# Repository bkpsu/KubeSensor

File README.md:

# KubeSensor
Kube - A modular, expandable home automation multi sensor platform

## Description

The Kube V2 builds on the previous [design](https://www.thingiverse.com/thing:2539897), incorporating improvements to modularity, support for additional sensors, and building ease.

##### Original Kube (left) and Kube V2 (right)

The main design improvement for Kube V2 is that all components are installed on dedicated PCBs, removing the need for wiring, and the PCBs are connected to each other via long headers, which allow the different "modules" to snap together to form a complete Kube.

##### OLED module (top) with male headers that snap into the base board (bottom) with tabs on the 3d printed enclosures holding the module in place

The 6-pin header is populated with I2C signals from the NodeMCU (D1/D2), D4 pin for LED control, and 5V and 3V3 power supply pins with ground. This allows building various different designs of the "stack", and future expansion of the Kube platform, via I2C connected "submodules". The design currently contains four modules, including:

1. Base module (with NodeMCU, breakout headers, 74HCT125N level shifter and external connectors/spots for DHT22 sensor)
2. Power Supply module (with AC/DC, DC/DC and POE-level power supply options, to provide the 5V power for the stack)
3. Analog/Digital IO module (offering expansion of Digital I/O up to 128 signals and 4 channels of 16-bit ADC analog)
4. OLED/AmbiMate sensor module (offering a 0.96" OLED screen for local sensor data display and support for the multiple sensor AmbiMate MS4 board from TE Connectivity)

##### Kube stack with boards 1 (Base Module) and 4 (OLED/AmbiMate) shown, comprising a multi sensor

The different boards can be stacked in any order (with OLED board on top, of course), and multiple ADIO boards can be stacked together to expand I/O up to 128 channels.

The Kube v2 supports typical ESP8266 firmwares, including [ESPEasy](https://www.letscontrolit.com/wiki/index.php?title=ESPEasy), as well as my original Kube [firmware](https://github.com/bkpsu/NodeMCU-Home-Automation-Sensor) (with minor changes for pin layout). With ESPEasy, the different sensors and OLED screen can be easily connected to home automation platofrms like [openHAB](https://www.openhab.org) or [HomeAssistant](https://www.home-assistant.io/) via MQTT.

---

## Boards

This section will describe the currently available Kube module boards in detail, including schematics and any jumper settings required for each board, as well as links to the parts required to build each module.

### 1. Kube Base Module

The Kube Base module is the only **required** board in the Kube stack. It contains the headers for a [NodeMCU](https://amzn.to/2l9GGET) v0.9, v2 (LoLin v3 works, but won't fit the enclosure), as well as breakout headers for all of the NodeMCU pins. With just the Kube Base module, a NodeMCU, a DHT22 sensor, and an OLED screen, you can create [this sensor](https://www.thingiverse.com/thing:2539897):

The base module contains the following features/headers:

**TOP**: (NodeMCU side)

|Device|Usage|Notes|
|:--------|:-----|-------|
|EXT|Used for external sensor connections, e.g. [HC-SR501](https://amzn.to/2l9G0zl) PIR motion sensor (D5 NodeMCU pin)|VCC pin is tied to JP1, sourcing either 3.3V or 5V DC|
|JP1|Selects 5V or 3.3V supply voltage for the EXT header|Does *not* affect D5 pin voltage range|
|IC1|[74HCT125N](https://amzn.to/2l9FBwP) 4-channel fast level shifter|Used for I2C/LED and EXT signal pins; Great for LED pixels|
|D1|[BAT43](https://amzn.to/2jFCRqv) Schottky Diode|Used between RST and D0 pins on the NodeMCU to prevent boot-up issues during flashing|
|DHT|[DHT22](https://amzn.to/2l98yZL) Temperature/Humidity sensor|Used when base baord is used as a remote temperature/humidity sensor; uses D6 pin on NodeMCU|
|I2C/LED|I2C bus connector header, to allow *daughter-boards* to connect to the Kube base board and to each other|Has both 5V and 3.3V pins, GND, SCL (D1) and SDA (D2), as well as an additional digital I/O pin (D4), commonly used in LED strip controller firmware|

**BOTTOM**:

|Device|Usage|Notes|
|:--------|:-----|-------|
|D1BYP, D2BYP|Used to shift (to 5V via IC1) or bypass (3.3V from the NodeMCU) the I2C Clock (D1, SCL) and Data (D2, SDA) pins within the I2C/LED header|Solder middle pad to either the SHFT (for 5V) or BYP (for 3.3v) pads.|
|D4BYP|Used to shift (to 5V via IC1) or bypass (3.3V from the NodeMCU) the D4 LED pin within the I2C/LED header|Solder middle pad to either the SHFT (for 5V) or BYP (for 3.3v) pads.|
|D5BYP|Used to shift (to 5V via IC1) or bypass (3.3V from the NodeMCU) the D5 EXT pin within the EXT sensor header|Solder middle pad to either the SHFT (for 5V) or BYP (for 3.3v) pads.|

The full schematic for the Kube baseboard is shown below: 

### 2. Power Supply Module

The Kube Power supply submodule offers several options to provide the 5VDC power required to run the NodeMCU and the entire Kube stack. It is *generally* not required, since it's perfectly fine to power the Kube with just a USB power supply via the NodeMCU's micro-USB port (accessible via a hole in the base module's enclosure), but if you're going to use more sensors, IO boards, or other external devices, it *is recommended* to supply power to the Kube stack via this PSU board module.

The Kube PS board module provides three possible configurations, each allowing different input voltages, with 5V DC output.

1. Using a [MeanWell IRM-03-5](https://amzn.to/2lbSsym) AC/DC power supply (110VAC in, 5VDC out) for a wall-pluggable unit
2. Using [MeanWell SLC03x](https://www.arrow.com/en/products/slc03b-05/mean-well-enterprises) series DC-DC power supplies for multiple input options (12j/24VDC, Power-over-Ethernet, etc)
3. Using a [Rectifier](https://amzn.to/2lin9SL) and a [Buck Converter](https://amzn.to/2lkQhZH) to convert low-voltage AC (e.g. a door bell transformer or HVAC thermostat power) to power the kube stack.

***NOTE***: **BE EXTREMELY CAREFUL WHEN USING THE KUBE PS MODULE WITH AC POWER. THE PCB TRACES ON THE BOTTOM OF THE BOARD WILL HAVE LIVE AC VOLTAGE ON THEM. IT IS BEST TO KEEP THE UNIT UNPLUGGED WHILE ASSEMBLING/DISSASEMBLING THE KUBE STACK.**

Regardless of which of the 3 power methods you're using, the power input wiring will go through the [2-pin screw terminal](https://amzn.to/2lhCMtC) (X1), with Line or DC+ on the left terminal, and Neutral or DC- on the right terminal. The line/DC+ line is [fuse-protected](https://amzn.to/2jPolfY) prior to going to the power supplies. Secure the input wiring with a zip-tie through the two holes drilled below the X1 connector.

The full schematic for the Kube Power Supply submodule is shown below:

### 3. Analog/Digital I/O module

The ADIO Kube submodule can be used when more I/O is required than the NodeMCU GPIO pins provide, or for a more precise way to bring in analog inputs into the Kube sensor.

The ADIO submodule provides space for the [MCP23017](https://amzn.to/2lg6Qpt) 16-channel digital I/O expander, as well as a [ADS1115](https://amzn.to/2lgUYDz) 4-channel 16-bit analog ADC module. In addition, the MCP23017 address pins have been broken out into three headers (AD0, AD1, AD2), which allow addressing up to 8 different MCP23017 chips. In theory, you could stack 8 ADIO submoodules in the Kube stack, for a total of 128 digital I/O pins!

##### Testing a full Kube stack with an analog differential pressure sensor connected to the ADIO submodule.

The MCP23017 addressing is handled via jumpers on the AD0, AD1 and AD2 headers. Jumpering the left pin to the middle pin sets that address bit HIGH (1) and jumpering the right pin to the middle pin sets it LOW (0). The following table shows the complete I2C address scheme based on jumper settings:

|AD0|AD1|AD2|I2C Address|
|---|---|---|-----|
|0|0|0|0x20|
|1|0|0|0x21|
|0|1|0|0x22|
|1|1|0|0x23|
|0|0|1|0x24|
|1|0|1|0x25|
|0|1|1|0x26|
|1|1|1|0x27|

The ADS1115 board is also addressable, using the AADDR headers. Select addresses 0x48, 0x49, 0x4A or 0x4B by placing a jumper across one set of the jumper pins. This way, up to 4 ADIO submodules may have ADS1115 breakouts installed, for a total of 16 analog input channels.

The rest of the devices on the ADIO submodule are described below:

|Device|Usage|Notes|
|:--------|:-----|-------|
|IC1|[MCP23017](https://amzn.to/2lg6Qpt) I/O Expander|16 channel digital I/O expander|
|ADS1115|[ADS1115](https://amzn.to/2lgUYDz)|4 channel 16-bit analog ADC module (can also use [ADS1015](https://amzn.to/2lcyVOj), 12-bit ADC)|
|X1|Channels 1 through 4 (top to bottom) of the MCP23017|Wired in using [4-pin screw terminals](https://amzn.to/2lc5hbY)|
|X2|Channels 5 through 8 (top to bottom) of the MCP23017|Wired in using [4-pin screw terminals](https://amzn.to/2lc5hbY)|
|X3|Channels 9 through 12 (top to bottom) of the MCP23017|Wired in using [4-pin screw terminals](https://amzn.to/2lc5hbY)|
|X4|Channels 13 through 16 (top to bottom) of the MCP23017|Wired in using [4-pin screw terminals](https://amzn.to/2lc5hbY)|
|X5|Channels 1 through 4 (top to bottom) of the ADS1115|Wired in using [4-pin screw terminals](https://amzn.to/2lc5hbY)|
|X6 & X7|GND terminals for the I/O signals|Wired in using [4-pin screw terminals](https://amzn.to/2lc5hbY)|
|X8|5V power terminals for the I/O signals|Wired in using [4-pin screw terminals](https://amzn.to/2lc5hbY)|
|I2C/LED|I2C bus connector header, to allow *daughter-boards* to connect to the Kube base board and to each other|Has both 5V and 3.3V pins, GND, SCL (D1) and SDA (D2), as well as an additional digital I/O pin (D4), commonly used in LED strip controller firmware|

The full schematic for the Kube IO submodule is shown below:

### 4. OLED/AmbiMate MS4 module

The OLED/AmbiMate submodule serves a dual purpose. It can provide a local display of all the Kube sensor values (if the OLED screen is installed), and with the optional TE AmbiMate MS4 sensor board installed, it can read values such as temperature/humidity/light/audio level/motion/CO2 level/VOCs level, and provide them via I2C to the NodeMCU. In lieu of the TE Ambimate MS4, a space is provided for the cheaper (but still very precise) BME280/BMP280 sensor board.

The [OLED display](https://amzn.to/2ll4BkL) used (0.96") provides a good canvas for displaying local sensor data. However, the boards used with these displays are not always standard. I have seen multiple versions of these boards, with different pinouts for the 4 pin i2C interface, e.g. GND/VCC/SCL/SDA or VCC/GND/SCL/SDA. To allow both boards to be installed on the submodule, there are 4 jumpers on the back of the board, that allow swapping of the GND/VCC pins, and SCL/SDA pins, to hopefully match any combination of pins on the widely available modules.

The devices that fit on this board are as follows:

**TOP**:

|Device|Usage|Notes|
|:--------|:-----|-------|
|OLED|[OLED 0.96" Display](https://amzn.to/2ll4BkL)|16 channel digital I/O expander|
|TE AmbiMate MS4 Sensor|[Full Version](https://www.arrow.com/en/products/2316852-2/te-connectivity) or [Base Version](https://www.arrow.com/en/products/2316851-1/te-connectivity) (Temp/Humidity/Light/Motion only)|Multi-sensor from TE, with temperature/humidity/motion/light/CO2/VOCs and audio level measurements|
|I2C/LED|I2C bus connector header, to allow *daughter-boards* to connect to the Kube base board and to each other|Has both 5V and 3.3V pins, GND, SCL (D1) and SDA (D2), as well as an additional digital I/O pin (D4), commonly used in LED strip controller firmware|
|BMX280|[BME280/BMP280](https://amzn.to/2ZcHmcq) I2C sensor connector header|Jumper SJ5 to correct VCC (3v3 or 5V) for your sensor|

**BOTTOM**:

|Device|Usage|Notes|
|:--------|:------|-------|
|SJ1|First OLED pin selector|Match GND or VCC with your OLED screen's first pin, and solder that side to the middle pad|
|SJ2|Second OLED pin selector|Match GND or VCC with your OLED screen's second pin, and solder that side to the middle pad|
|SJ3|Third OLED pin selector|Match SCL or SDA with your OLED screen's third pin, and solder that side to the middle pad|
|SJ4|Fourth OLED pin selector|Match SCL or SDA with your OLED screen's fourth pin, and solder that side to the middle pad|
|SJ5|BMx280 sensor VCC selector|If using the 4-pin (5V) unit, jumper middle pad to 5v pad, and for 6-pin (3v3) unit, jumper middle pad to 3v3 pad|

The full schematic for the Kube OLED/AmbiMate submodule is shown below:

---

## Software

Use [ESPEasy](https://www.letscontrolit.com/espeasy/) firmware to easily connect the different sensors to the NodeMCU, and send them to your favorite database, or home automation program.

---

## BOM

Full, up to date BOM is available [here](Kube_V2_BOM.xlsx).

Get the PCB Boards directly from [PCBWay](https://www.pcbway.com/project/member/?bmbno=74C10494-455E-47)!

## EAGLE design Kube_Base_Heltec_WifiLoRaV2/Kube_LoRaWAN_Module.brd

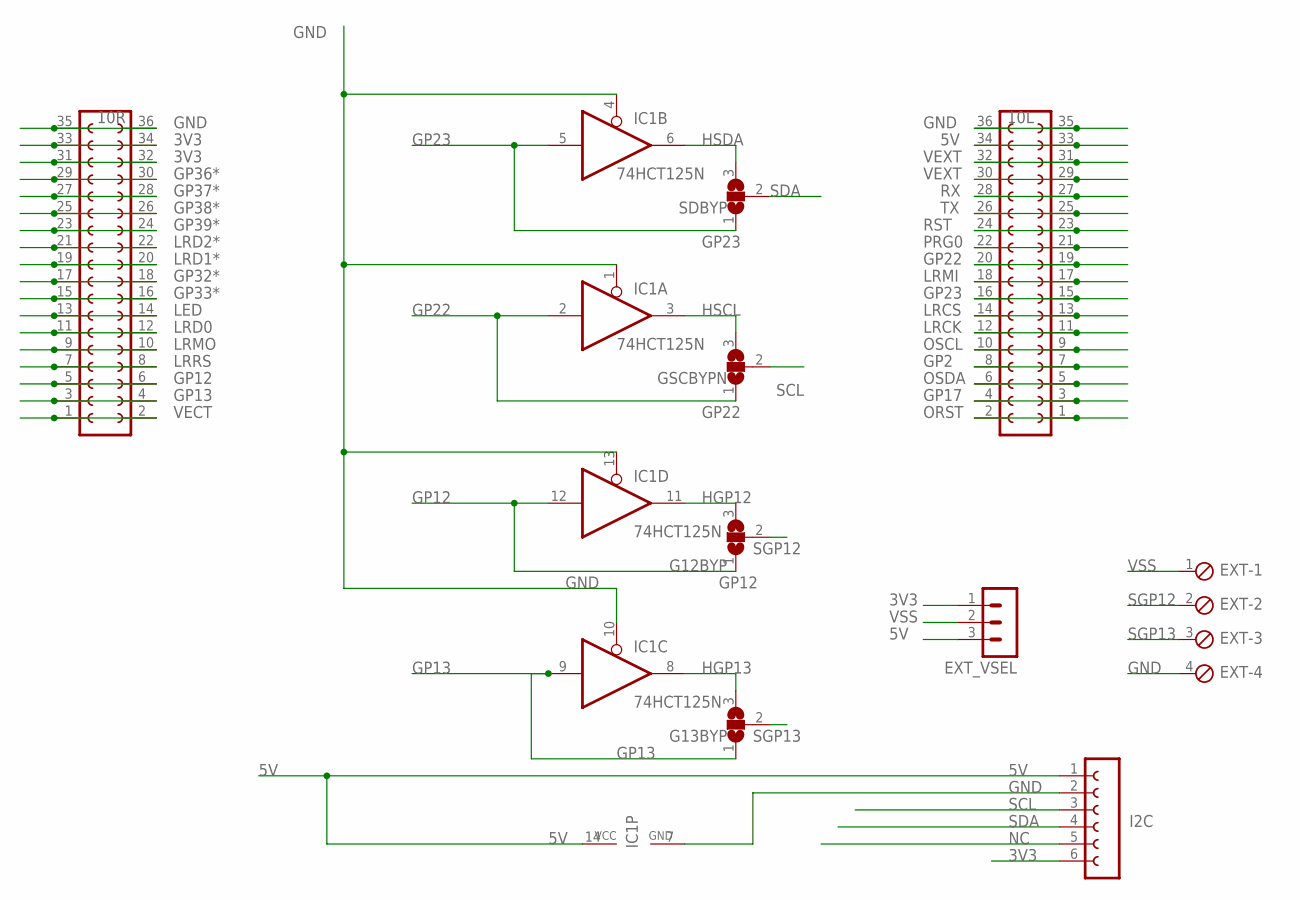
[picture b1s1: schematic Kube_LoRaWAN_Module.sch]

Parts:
10L, 10R: 15; FE18-2
EXT: MPT4; 4POL254
EXT_VSEL: MA03-1
G12BYP, G13BYP: SJ2W; SJ_2
GSCBYPN: SJ2W; SJ_2
I2C: FE06-1; FE06
IC1: 74HCT125N; DIL14
SDBYP: SJ2W; SJ_2

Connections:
3V3: 10R.31, 10R.32, 10R.33, 10R.34, EXT_VSEL.1, I2C.6
5V: 10L.33, 10L.34, EXT_VSEL.3, I2C.1, IC1.14 (VCC)
GND: 10L.35, 10L.36, 10R.35, 10R.36, EXT.4, I2C.2, IC1.1 (OE), IC1.4 (OE), IC1.7 (GND), IC1.10 (OE), IC1.13 (OE)
GP2: 10L.7, 10L.8
GP12: 10R.5, 10R.6, G12BYP.1, IC1.12 (I)
GP13: 10R.3, 10R.4, G13BYP.1, IC1.9 (I)
GP17: 10L.3, 10L.4
GP22: 10L.19, 10L.20, GSCBYPN.1, IC1.2 (I)
GP23: 10L.15, 10L.16, IC1.5 (I), SDBYP.1
GP32*: 10R.17, 10R.18
GP33*: 10R.15, 10R.16
GP36*: 10R.29, 10R.30
GP37*: 10R.27, 10R.28
GP38*: 10R.25, 10R.26
GP39*: 10R.23, 10R.24
HGP12: G12BYP.3, IC1.11 (O)
HGP13: G13BYP.3, IC1.8 (O)
HSCL: GSCBYPN.3, IC1.3 (O)
HSDA: IC1.6 (O), SDBYP.3
LED: 10R.13, 10R.14
LRCK: 10L.11, 10L.12
LRCS: 10L.13, 10L.14
LRD0: 10R.11, 10R.12
LRD1*: 10R.19, 10R.20
LRD2*: 10R.21, 10R.22
LRMI: 10L.17, 10L.18
LRMO: 10R.9, 10R.10
LRRS: 10R.7, 10R.8
NC: I2C.5
ORST: 10L.1, 10L.2
OSCL: 10L.9, 10L.10
OSDA: 10L.5, 10L.6
PRG0: 10L.21, 10L.22
RST: 10L.23, 10L.24
RX: 10L.27, 10L.28
SCL: GSCBYPN.2, I2C.3
SDA: I2C.4, SDBYP.2
SGP12: EXT.2, G12BYP.2
SGP13: EXT.3, G13BYP.2
TX: 10L.25, 10L.26
VECT: 10R.1, 10R.2
VEXT: 10L.29, 10L.30, 10L.31, 10L.32
VSS: EXT.1, EXT_VSEL.2

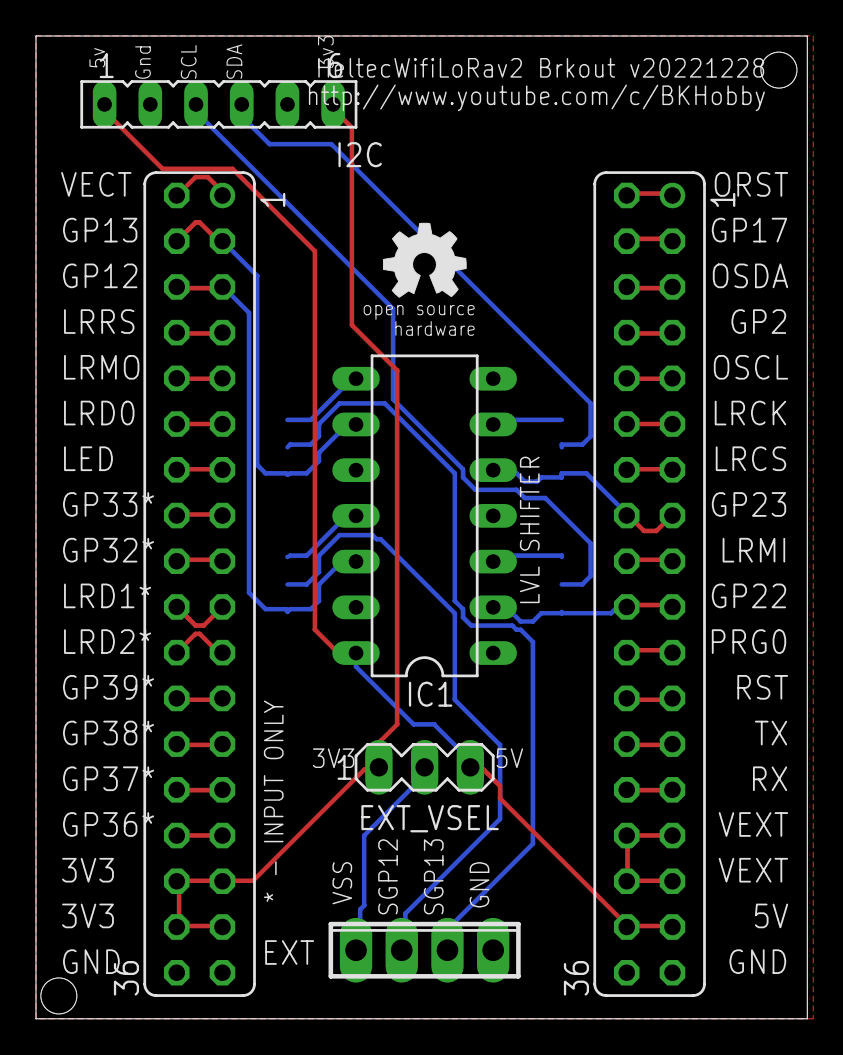
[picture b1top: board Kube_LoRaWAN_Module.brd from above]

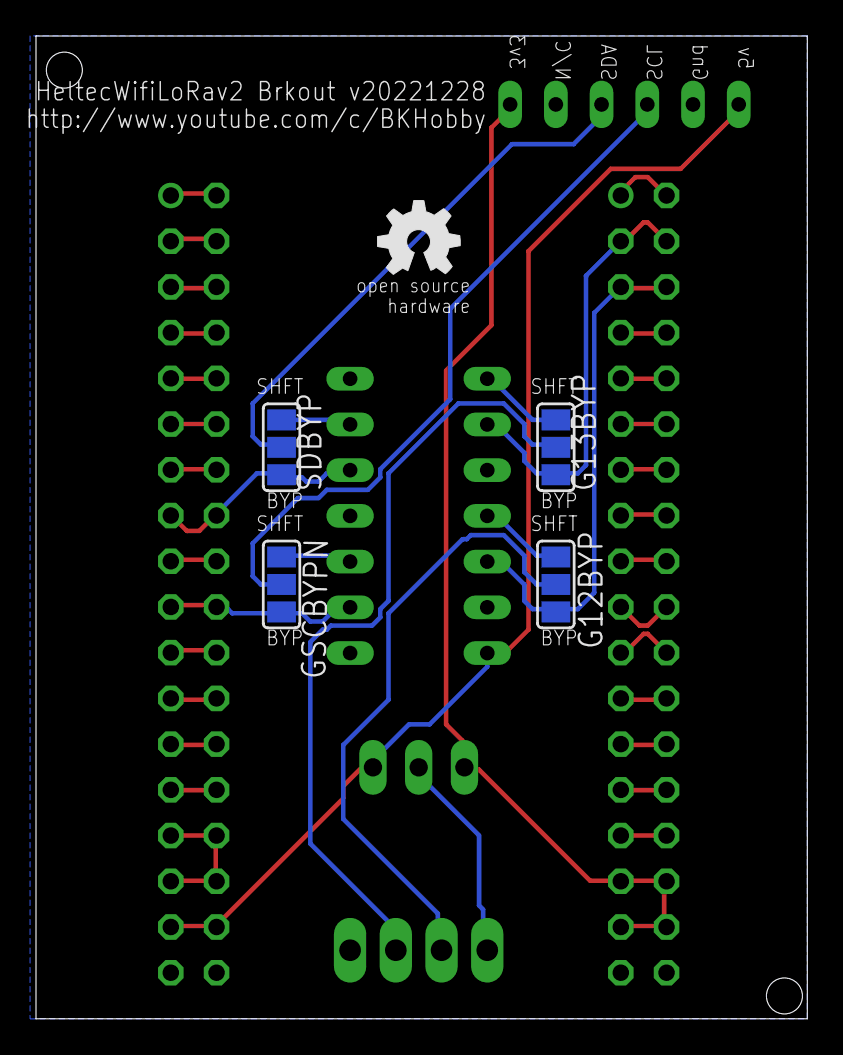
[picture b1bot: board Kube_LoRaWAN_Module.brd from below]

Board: 2 copper layers, 42.8 x 54.6 mm, 12 parts (5 on the bottom side), 42 nets.

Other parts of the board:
U$1, U$2: OSHW_5MM

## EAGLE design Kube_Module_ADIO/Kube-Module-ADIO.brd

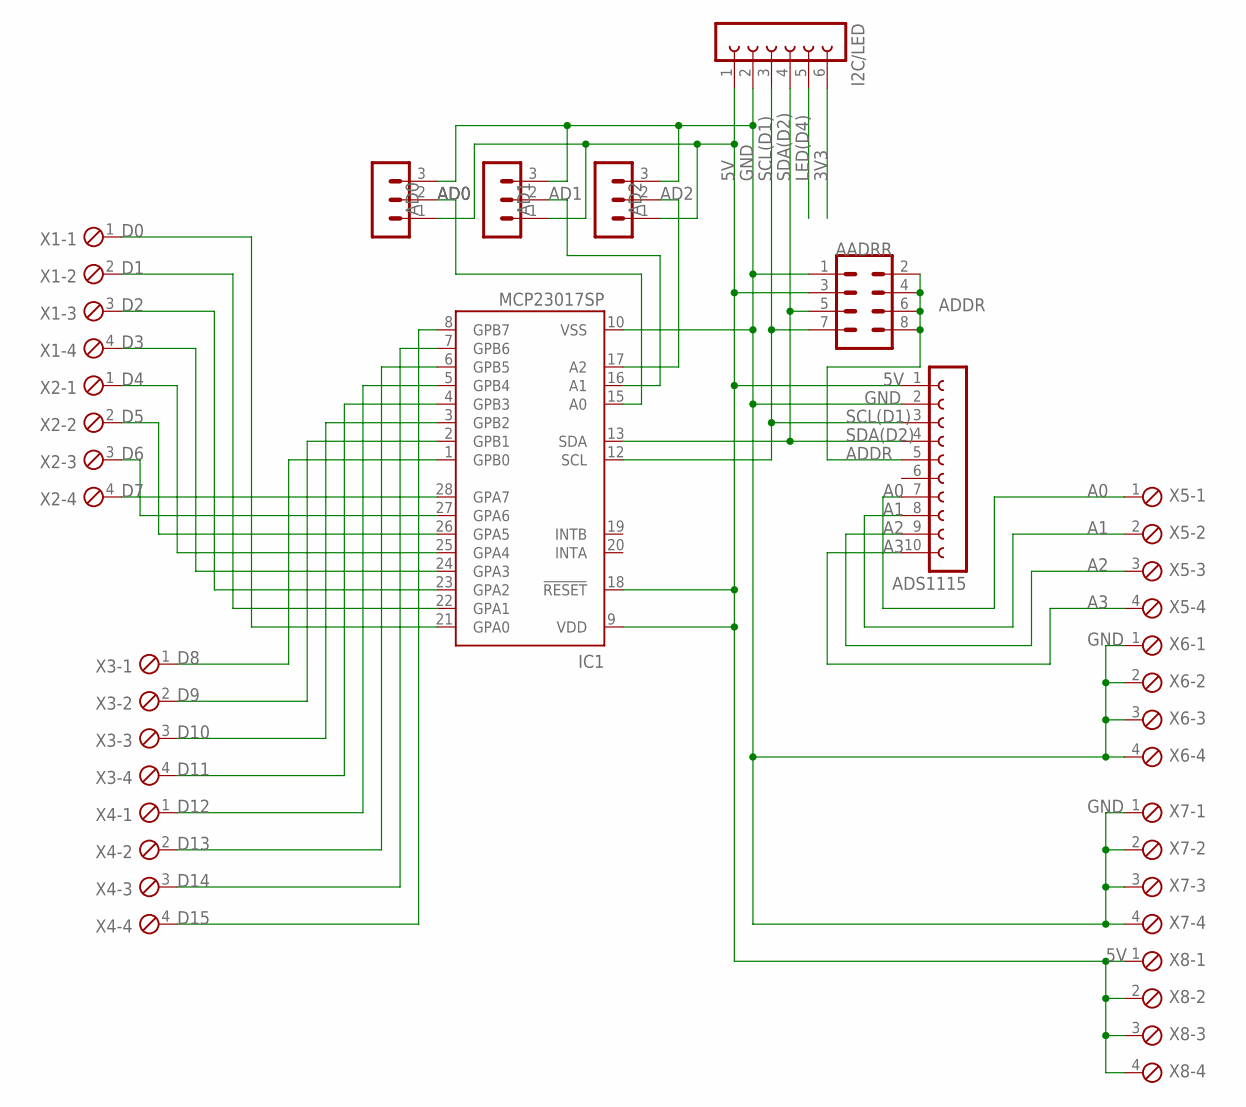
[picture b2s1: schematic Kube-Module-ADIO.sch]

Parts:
AADRR: MA04-2
AD0, AD1, AD2: MA03-1
ADS1115: FE10W
I2C/LED: FE06-1; FE06
IC1: MCP23017SP; DIL28-3
X1, X2, X3, X4, X5, X6, X7, X8: MPT4; 4POL254

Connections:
3V3: I2C/LED.6
5V: AADRR.3, AD0.1, AD1.1, AD2.1, ADS1115.1, I2C/LED.1, IC1.9 (VDD), IC1.18 (!RESET), X8.1, X8.2, X8.3, X8.4
A0: ADS1115.7, X5.1
A1: ADS1115.8, X5.2
A2: ADS1115.9, X5.3
A3: ADS1115.10, X5.4
AD0: AD0.2, IC1.15 (A0)
AD1: AD1.2, IC1.16 (A1)
AD2: AD2.2, IC1.17 (A2)
ADDR: AADRR.2, AADRR.4, AADRR.6, AADRR.8, ADS1115.5
D0: IC1.21 (GPA0), X1.1
D1: IC1.22 (GPA1), X1.2
D2: IC1.23 (GPA2), X1.3
D3: IC1.24 (GPA3), X1.4
D4: IC1.25 (GPA4), X2.1
D5: IC1.26 (GPA5), X2.2
D6: IC1.27 (GPA6), X2.3
D7: IC1.28 (GPA7), X2.4
D8: IC1.1 (GPB0), X3.1
D9: IC1.2 (GPB1), X3.2
D10: IC1.3 (GPB2), X3.3
D11: IC1.4 (GPB3), X3.4
D12: IC1.5 (GPB4), X4.1
D13: IC1.6 (GPB5), X4.2
D14: IC1.7 (GPB6), X4.3
D15: IC1.8 (GPB7), X4.4
GND: AADRR.1, AD0.3, AD1.3, AD2.3, ADS1115.2, I2C/LED.2, IC1.10 (VSS), X6.1, X6.2, X6.3, X6.4, X7.1, X7.2, X7.3, X7.4
LED(D4): I2C/LED.5
SCL(D1): AADRR.7, ADS1115.3, I2C/LED.3, IC1.12 (SCL)
SDA(D2): AADRR.5, ADS1115.4, I2C/LED.4, IC1.13 (SDA)

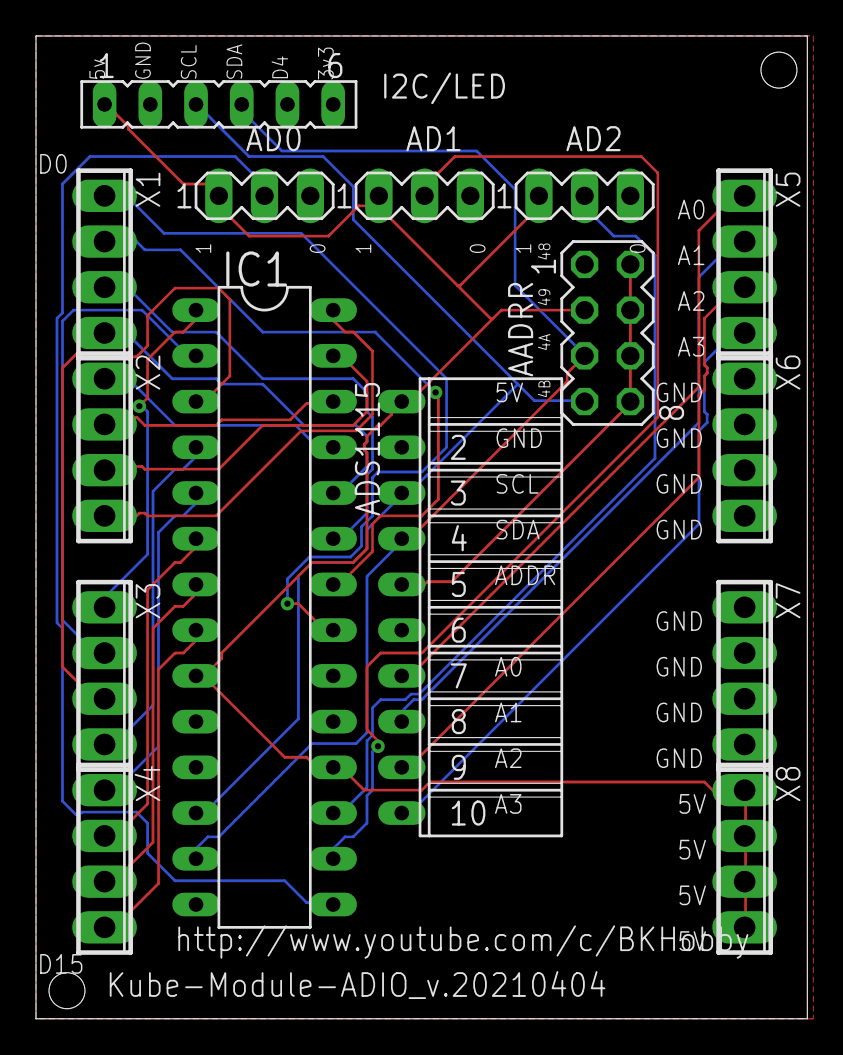
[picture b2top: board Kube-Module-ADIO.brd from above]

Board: 2 copper layers, 42.8 x 54.6 mm, 15 parts (0 on the bottom side), 28 nets.

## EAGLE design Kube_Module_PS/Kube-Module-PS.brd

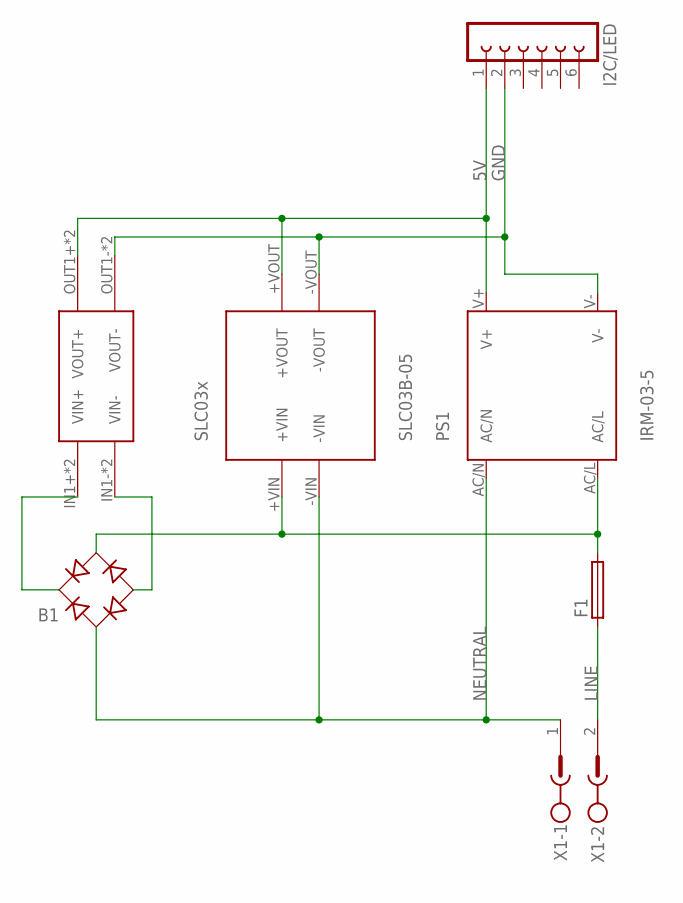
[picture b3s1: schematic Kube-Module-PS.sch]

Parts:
B1: RB1A
F1: LITTLEFUSE
I2C/LED: FE06-1; FE06
MP1584: MP1584; DC-BRICK
PS1: IRM-03-5; IRM_03
SLC03X: SLC03B-05; SLC03X
X1: MSTBV2

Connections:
5V: I2C/LED.1, MP1584.OUT1+ (VOUT+), MP1584.OUT2+ (VOUT+), PS1.V+, SLC03X.+VOUT
GND: I2C/LED.2, MP1584.OUT1- (VOUT-), MP1584.OUT2- (VOUT-), PS1.V-, SLC03X.-VOUT
LINE: F1.1, X1.2
LINE-FUSED: B1.AC2, F1.2, PS1.AC/L, SLC03X.+VIN
NEUTRAL: B1.AC1, PS1.AC/N, SLC03X.-VIN, X1.1
V+: B1.+, MP1584.IN1+ (VIN+), MP1584.IN2+ (VIN+)
V-: B1.-, MP1584.IN1- (VIN-), MP1584.IN2- (VIN-)

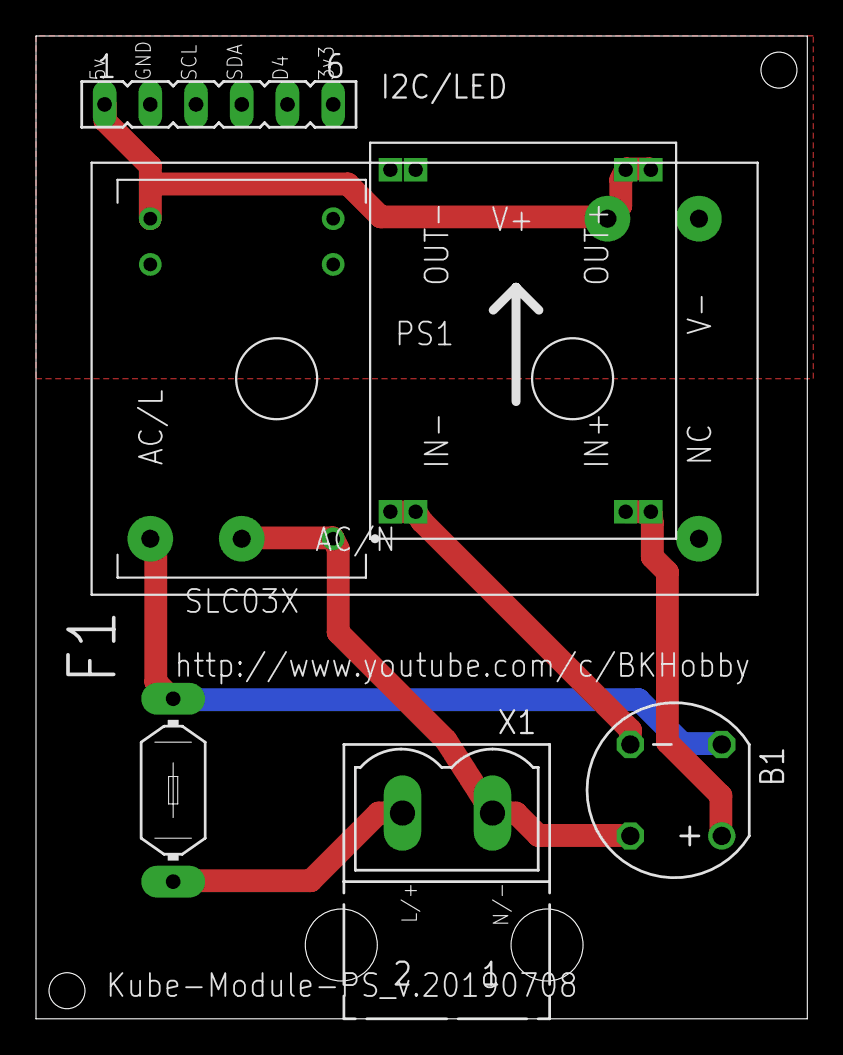
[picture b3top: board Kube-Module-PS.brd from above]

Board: 2 copper layers, 42.8 x 54.6 mm, 7 parts (0 on the bottom side), 7 nets.

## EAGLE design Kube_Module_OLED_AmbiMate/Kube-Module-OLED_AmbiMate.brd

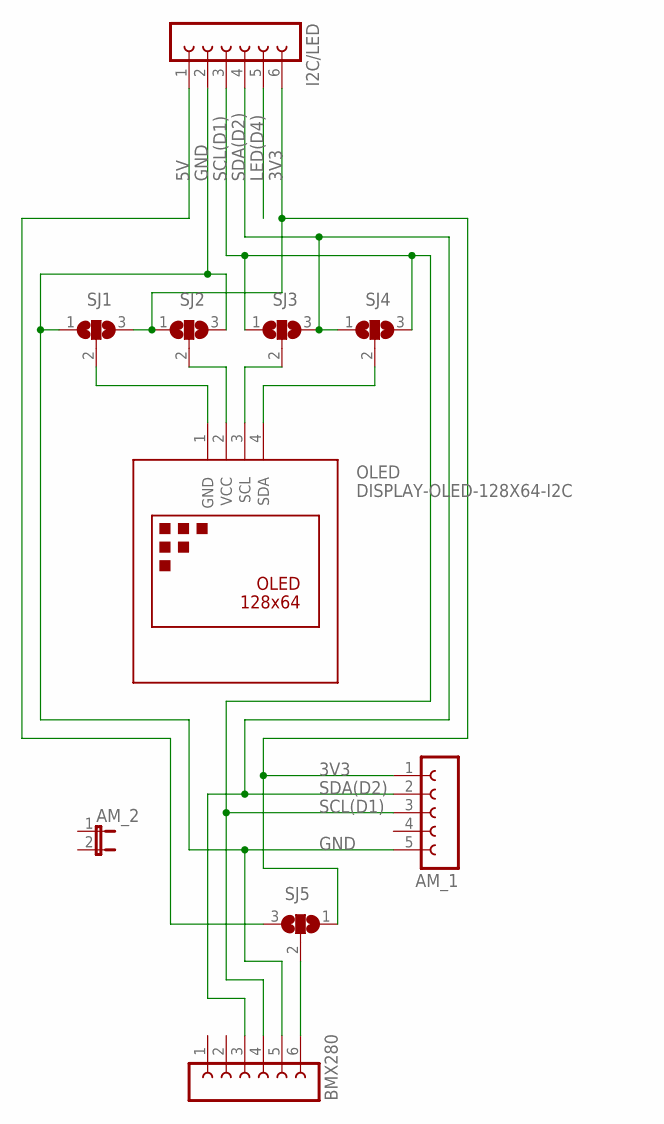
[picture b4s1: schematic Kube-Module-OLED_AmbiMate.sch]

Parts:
AM_1: FE05-1
AM_2: JP1E; JP1
BMX280: FE06-1; FE06
I2C/LED: FE06-1; FE06
OLED: DISPLAY-OLED-128X64-I2C
SJ1, SJ2, SJ3, SJ4, SJ5: SJ2W; SJ_2

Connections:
3V3: AM_1.1, I2C/LED.6, SJ1.3, SJ2.1, SJ5.1
5V: I2C/LED.1, SJ5.3
BMX_VCC: BMX280.6, SJ5.2
GND: AM_1.5, BMX280.5, I2C/LED.2, SJ1.1, SJ2.3
LED(D4): I2C/LED.5
OP1: OLED.1 (GND), SJ1.2
OP2: OLED.2 (VCC), SJ2.2
OP3: OLED.3 (SCL), SJ3.2
OP4: OLED.4 (SDA), SJ4.2
SCL(D1): AM_1.3, BMX280.4, I2C/LED.3, SJ3.1, SJ4.3
SDA(D2): AM_1.2, BMX280.3, I2C/LED.4, SJ3.3, SJ4.1

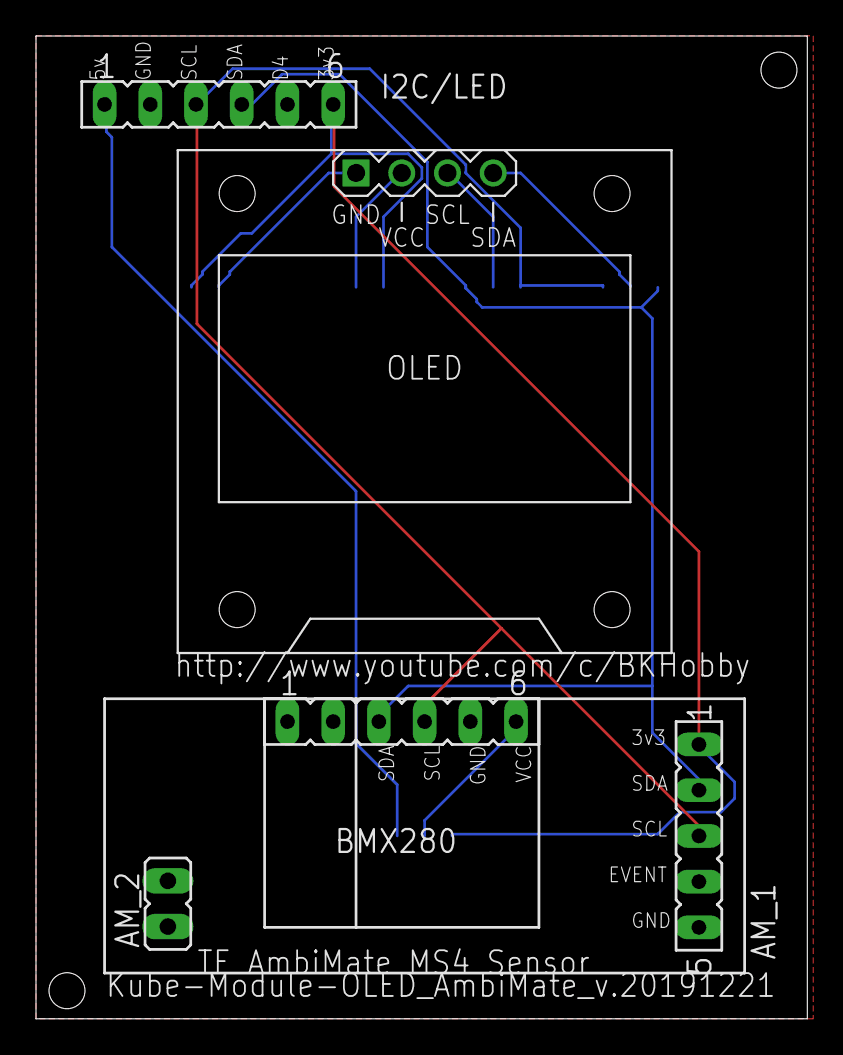
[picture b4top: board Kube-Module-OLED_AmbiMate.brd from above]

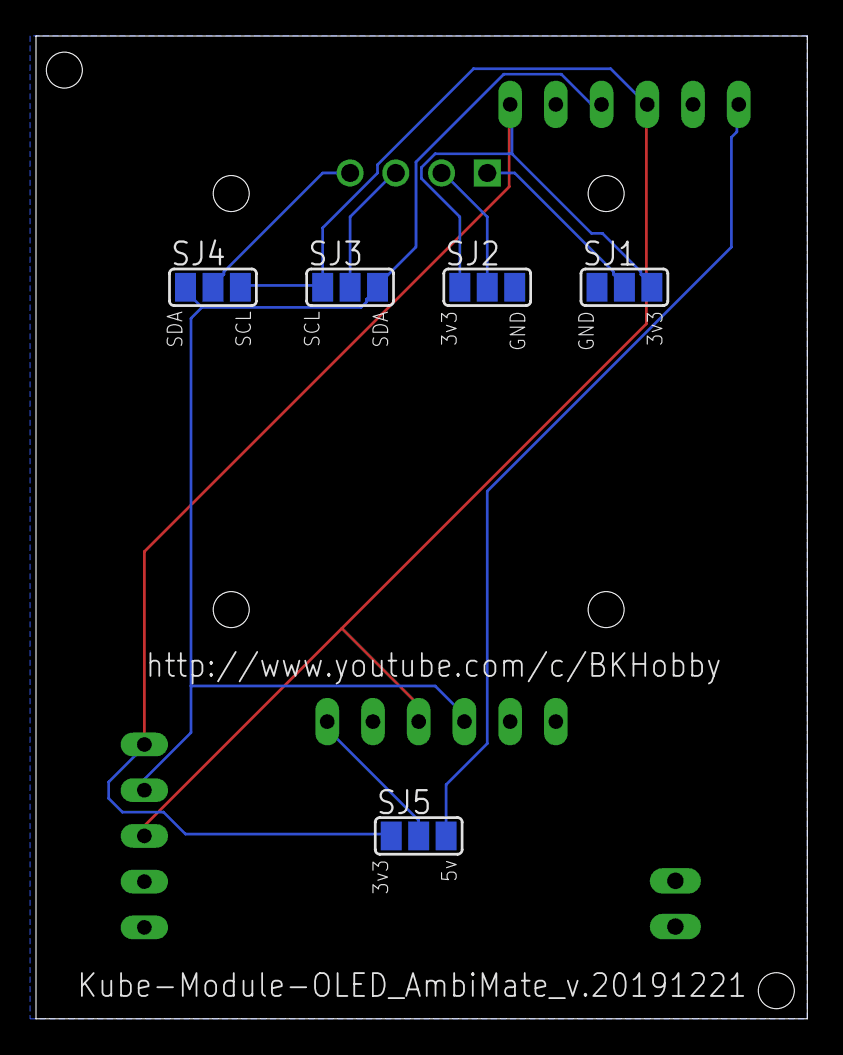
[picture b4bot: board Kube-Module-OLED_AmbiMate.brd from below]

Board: 2 copper layers, 42.8 x 54.6 mm, 10 parts (5 on the bottom side), 10 nets.

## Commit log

2019-07-09 Initial Upload
2019-07-09 Adding 3d models for the Base module, back cover and OLED submodule
2019-07-11 Adding Gerber files, gitignore and new Readme
2019-07-11 Updated gitignore
2019-07-11 Readme
2019-07-13 Added some board definition paragraphs/pictures.
2019-07-13 Fixed tables
2019-07-13 HW build instructions added (thanks rahimlee54!)
2019-07-14 More changes to Readme, regenerated ADIO Gerbers
2019-07-15 Finished OLED section
2019-07-15 Fixed some table issues.
2019-07-25 Set theme jekyll-theme-cayman
2019-07-25 Mods to ADIO to add add'l GND pins and space TBs better.
2019-07-25 Mods to OLED board to get rid of EVENT_OUT (causes boot issues since D4 needs to be held HI)
2019-07-25 Fixed Readme to account for OLED/ADIO changes
2019-07-25 Fixed schematics
2019-07-25 Img fixes
2019-07-25 More img fixes
2019-08-03 All updated STLs, and ADIO board with tb fixes.
2019-12-22 Added BMx280 sensor to OLED Board
2019-12-22 Updated readme for OLED changes, new PCB renders
2020-04-25 Adding Fusion360 files for all modules
2021-04-05 Added ADS1115 addressing jumper
2021-04-05 Added LoRaWan (Heltec) board
2021-04-05 Updated ADIO image with AADDR header
2021-04-05 More ADIO updates
2024-11-28 11/28/2024(BK): Merging all changes on remote

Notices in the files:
parts and their libraries:
diy-modules: Released under the Creative Commons Attribution 4.0 International License: http://creativecommons.org/licenses/by/4.0
